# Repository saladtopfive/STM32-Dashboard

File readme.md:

# 🚘 STM32 Go-Kart Dashboard  

> [!IMPORTANT]  
> **Work suspended** — Development suspended as of **07.08.2026**  
> This repository is part of my **Engineering Thesis Project** for the completion of my undergraduate studies.  

## Overview  

This project constitutes the practical component of my **engineering thesis**, focusing on the design and implementation of a **real-time dashboard system** for an electric go-kart.  

The system is developed on the **STM32F746G-DISCO microcontroller** with a touchscreen display using **TouchGFX**, and is intended to collect, process, and visualize telemetry data from multiple hardware sensors.  

The dashboard serves as a **human–machine interface (HMI)**, enabling the driver to monitor essential parameters of the vehicle in real time. These include, but are not limited to:  

## Preview

| Main Screen | Error Table |
|------------|-------------|
|  |  |

| Temperature Table | Battery Table |
|-----------------|----------------|
|  |  |

## Monitored Metrics  

| ***Metric***                | ***Description***                                |
|------------------------|--------------------------------------------|
| **Vehicle Speed**          | Real-time speed display.                   |
| **Throttle / Brake**       | Input level visualization.                  |
| **Battery**                | Voltage and temperature monitoring.         |
| **Motor Temperature**      | Prevents overheating and ensures reliability. |
| **G-Forces**               | Lateral and vertical forces in real time.   |
| **BMS Data (External)**    | Additional telemetry provided by an external Battery Management System (BMS), developed as a separate thesis project. This work only focuses on visualization of the received data. |
| **HOTLAP Button**           | Initiates a lap timer (stopwatch) in the dashboard, showing minutes, seconds, and centiseconds. Useful for tracking lap times during testing or racing sessions. |
| **Future Extensions**      | Additional sensor integrations planned.     |

The objective of this work is to provide a **robust, responsive, and intuitive interface** that supports safe and efficient operation of the electric go-kart.  

## Hardware

As part of the project, a custom **Arduino Shield** is being developed to handle all sensor inputs, signal routing, and electrical interfacing between the go-kart hardware and the STM32 dashboard.  

### KiCad Schematic Preview

### KiCad 3D Model Preview

### IRL pictures

| STM32 - dashboard | Shield |
|------------|-------------|
|  |  |

## Development Notes  

The project was initially developed without version control, with the focus placed on prototyping and interface design. 

As the implementation approaches the stage of **hardware integration**, this repository has been introduced to serve as a platform for:  

- Source code management and tracking.  
- Documentation of development progress. 
- Collaboration and versioning.  

## Roadmap  

| ***Status***    | ***Task*** |
|-----------|------|
|  **Done**   | Acquisition of the go-kart frame. |
|  **Done**   | Development of the UI prototype. |
|  **Ongoing** | Live sensor data implementation. |
|  **Ongoing** | Development of an export data feature. |
|  **Ongoing** | Implementation of battery management visualization. |
|  **Planned** | Integration of BLDC motor control. |

## License
This project is licensed under the MIT permissive license.

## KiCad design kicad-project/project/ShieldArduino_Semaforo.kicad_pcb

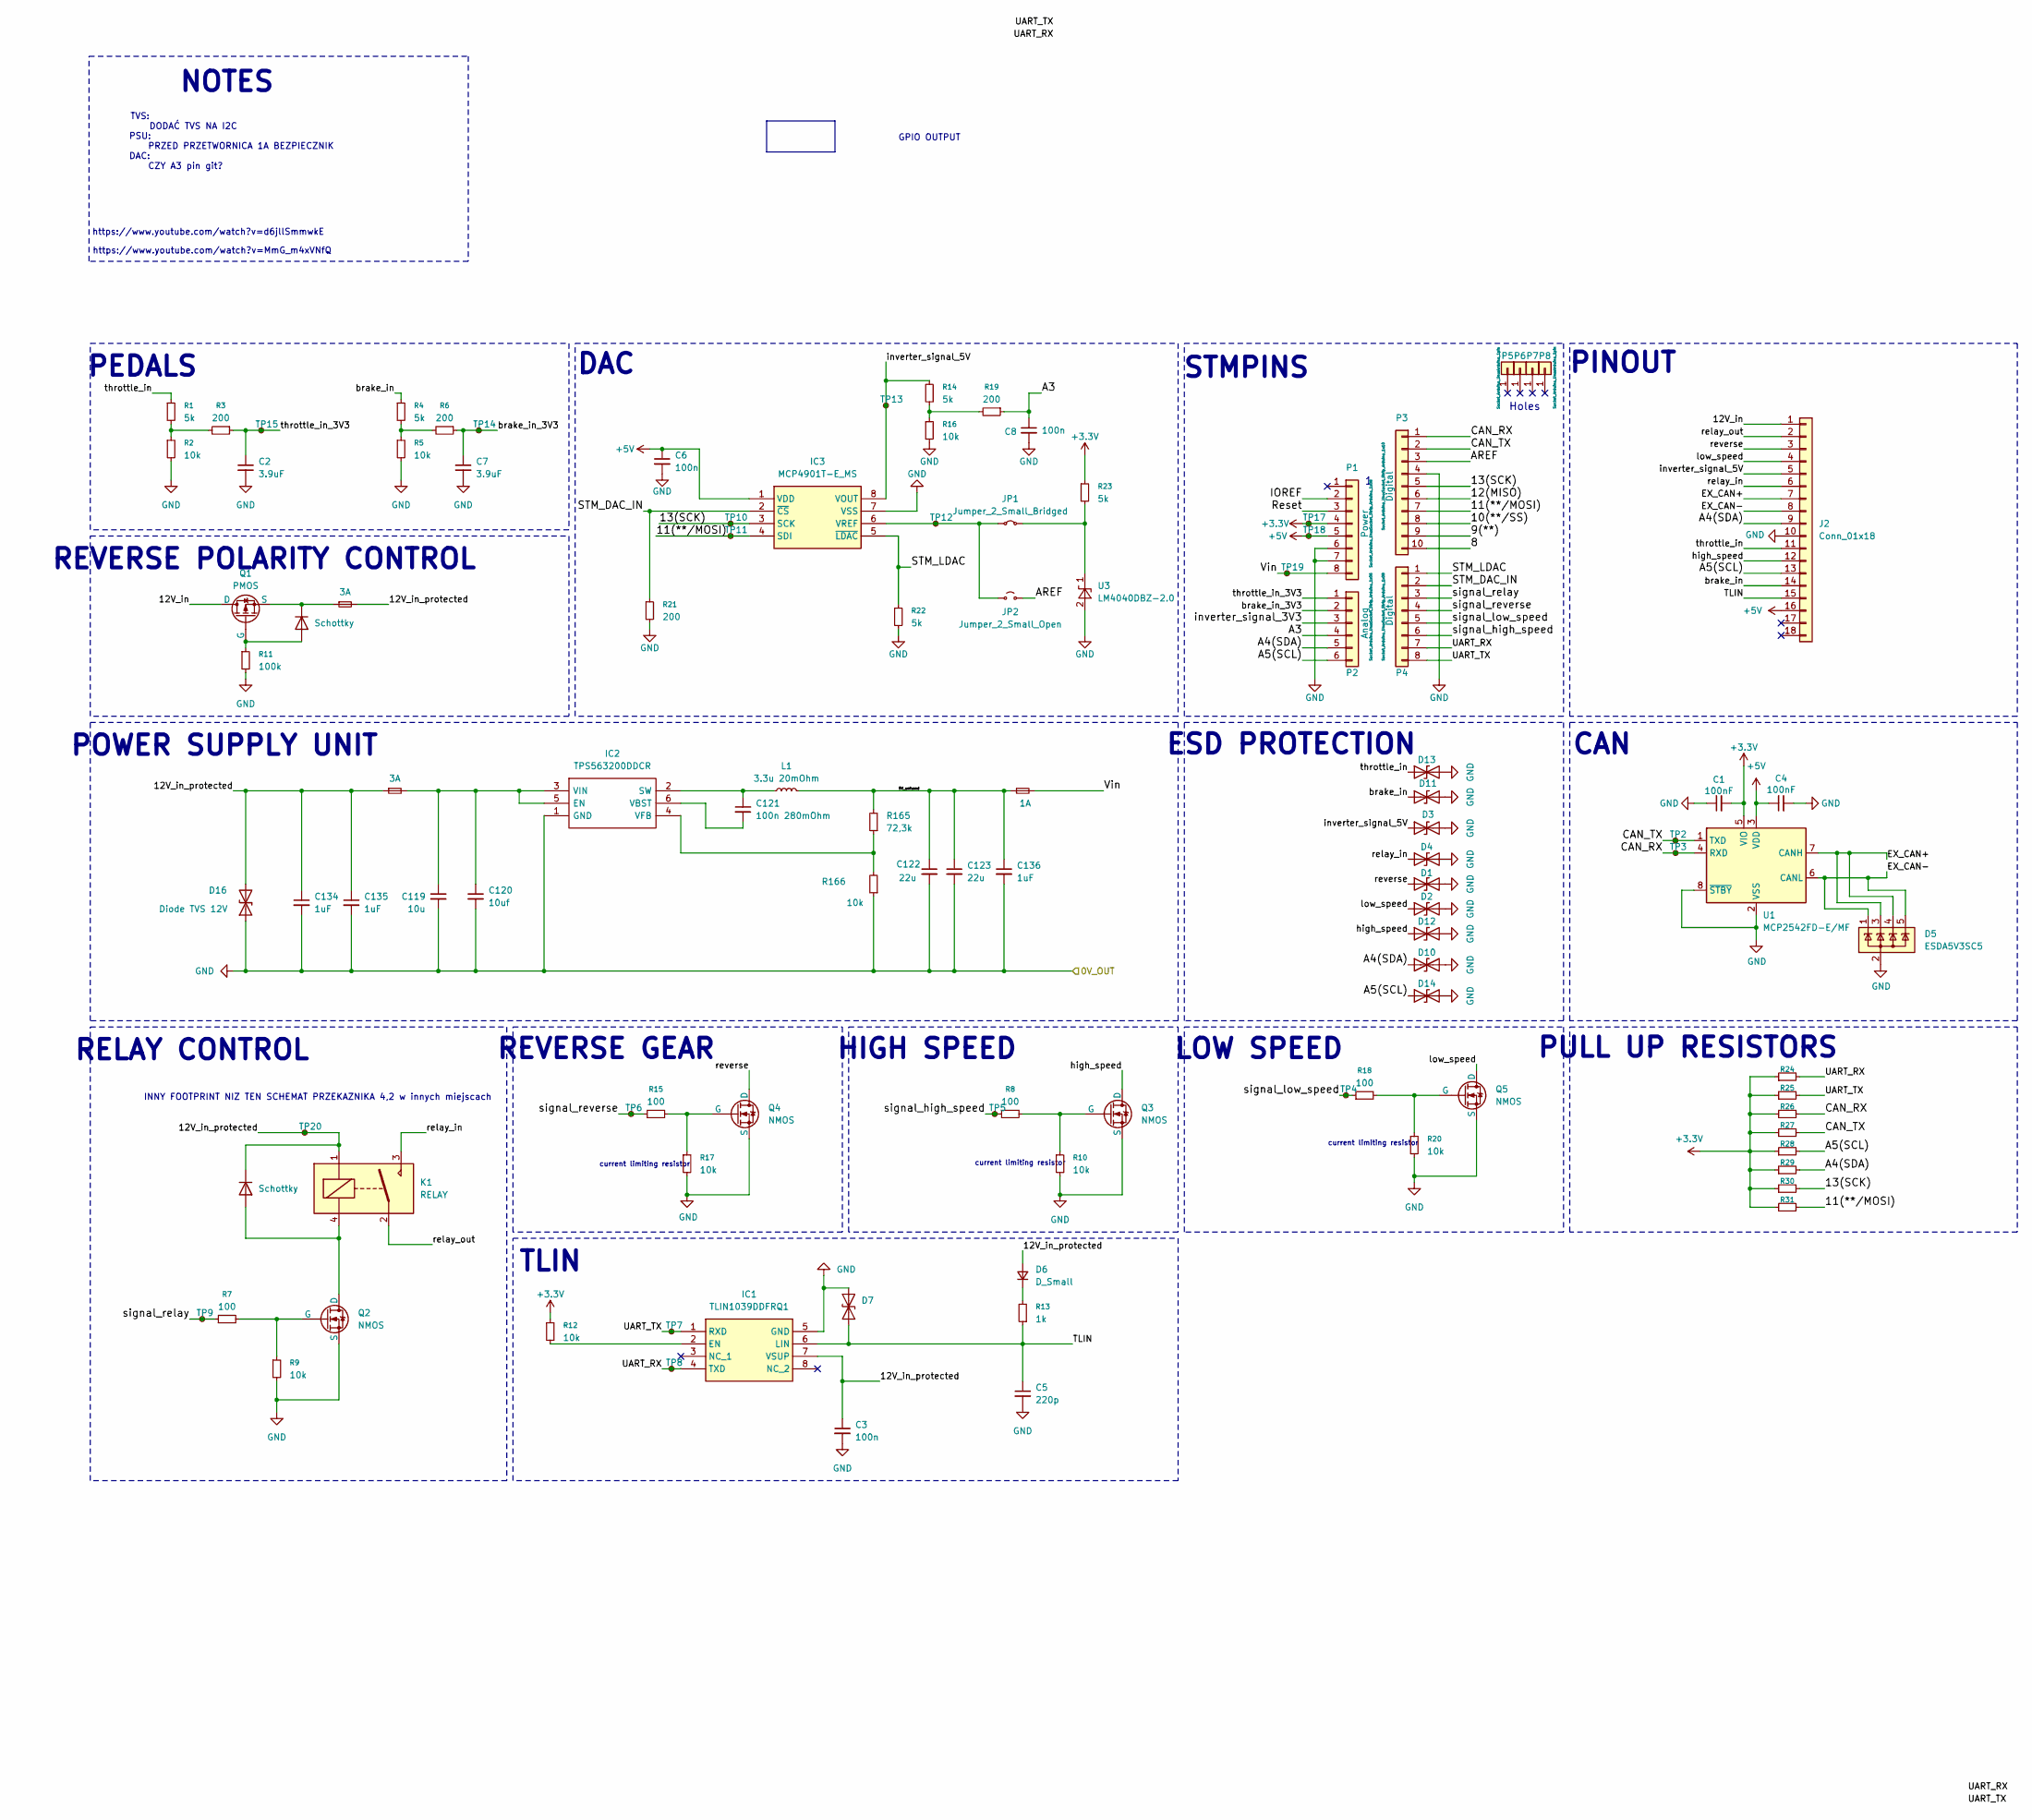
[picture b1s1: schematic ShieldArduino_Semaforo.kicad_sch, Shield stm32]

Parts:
C1, C4: 100nF; C_0603_1608Metric_Pad1.08x0.95mm_HandSolder; Manufacturer_Part_Number --; Mouser Part Number --
C2, C7: 3.9uF; C_1206_3216Metric_Pad1.33x1.80mm_HandSolder
C3, C6, C8: 100n; C_0805_2012Metric_Pad1.18x1.45mm_HandSolder
C5: 220p; C_0805_2012Metric_Pad1.18x1.45mm_HandSolder
C119: 10u; C_0805_2012Metric_Pad1.18x1.45mm_HandSolder
C120: 10uf; C_0805_2012Metric_Pad1.18x1.45mm_HandSolder
C121: 100n 280mOhm; C_0805_2012Metric_Pad1.18x1.45mm_HandSolder
C122, C123: 22u; C_0603_1608Metric_Pad1.08x0.95mm_HandSolder
C134, C135, C136: 1uF; C_0603_1608Metric_Pad1.08x0.95mm_HandSolder
D1, D2, D3, D4, D10, D11, D12, D13, D14: 6V; D_SOD-123F
D5: ESDA5V3SC5; SOT-23-5
D6: D_Small; SODFL3618X100N
D7: ESD131-B1-W0201; SOD2613X100N
D8, D9: Schottky; D_SOD-123
D16: Diode TVS 12V; D_SOD-323_HandSoldering
F1, F3: 3A; Fuse_0603_1608Metric_Pad1.05x0.95mm_HandSolder
F4: 1A; Fuse_0603_1608Metric_Pad1.05x0.95mm_HandSolder
IC1: TLIN1039DDFRQ1; SOT65P280X110-8N; Mouser Part Number 595-TLIN1039DDFRQ1
IC2: TPS563200DDCR; Mouser Part Number 595-TPS563200DDCR
IC3: MCP4901T-E_MS; SOP65P490X110-8N; Mouser Part Number 579-MCP4901T-E/MS
J2: Conn_01x18; M80-54016YY
JP1: Jumper_2_Small_Bridged; SolderJumper-2_P1.3mm_Bridged_RoundedPad1.0x1.5mm
JP2: Jumper_2_Small_Open; SolderJumper-2_P1.3mm_Open_RoundedPad1.0x1.5mm
K1: RELAY; RE034012
L1: 3.3u 20mOhm; CLF7045__
P1: Power; Socket_Strip_Arduino_1x08
P2: Analog; Socket_Strip_Arduino_1x06
P3: Digital; Socket_Strip_Arduino_1x10
P4: Digital; Socket_Strip_Arduino_1x08
P5, P6, P7, P8: CONN_01X01; Arduino_1pin
Q1: PMOS; SOT-23-3
Q2, Q3, Q4, Q5: NMOS; SOT-23-3
R1, R4, R14, R22, R23: 5k; R_0603_1608Metric_Pad0.98x0.95mm_HandSolder
R2, R5, R16, R166: 10k; R_0603_1608Metric_Pad0.98x0.95mm_HandSolder
R3, R6, R19, R21: 200; R_0603_1608Metric_Pad0.98x0.95mm_HandSolder
R7, R8, R15, R18: 100; R_0805_2012Metric_Pad1.20x1.40mm_HandSolder
R9, R10, R12, R17, R20, R24, R25, R26, R27, R28, R29, R30, R31: 10k; R_0805_2012Metric_Pad1.20x1.40mm_HandSolder
R11: 100k; R_0805_2012Metric_Pad1.20x1.40mm_HandSolder
R13: 1k; R_0805_2012Metric_Pad1.20x1.40mm_HandSolder
R165: 72,3k; R_0603_1608Metric_Pad0.98x0.95mm_HandSolder
TP2, TP3, TP4, TP5, TP6, TP7, TP8, TP9, TP10, TP11, TP12, TP13, TP14, TP15, TP17, TP18, TP19, TP20: TestPoint_Small; TestPoint_Pad_D1.5mm
U1: MCP2542FD-E/MF; SOIC127P600X175-8N; Manufacturer_Part_Number MCP2542FD-E/MF; Mouser Part Number 579-MCP2542FD-E/MF
U3: LM4040DBZ-2.0; SOT-23

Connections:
+3.3V: C1.2, P1.4, R12.1, R23.1, R24.1, R25.1, R26.1, R27.1, R28.1, R29.1, R30.1, R31.1, TP17.1, U1.5 (VIO)
+5V: C4.1, C6.1, IC3.1 (VDD), J2.16, P1.5, TP18.1, U1.3 (VDD)
/5V_unfused: C122.1, C123.1, C136.1, F4.1, L1.2, R165.2
/8: P3.10
/9(**): P3.9
/10(**/SS): P3.8
/11(**/MOSI): IC3.4 (SDI), P3.7, R31.2, TP11.1
/12(MISO): P3.6
/12V_in: J2.1, Q1.1 (D)
/12V_in_protected: C3.1, C134.1, C135.1, D6.2 (A), D8.1 (K), D16.2 (A2), F1.2, F3.1, IC1.7 (VSUP), K1.1, TP20.1
/13(SCK): IC3.3 (SCK), P3.5, R30.2, TP10.1
/ relay_in: D4.1 (A1), J2.6, K1.3
/A3: C8.1, P2.4, R19.1
/A4(SDA): D10.1 (A1), J2.9, P2.5, R29.2
/A5(SCL): D14.1 (A1), J2.13, P2.6, R28.2
/AREF: JP2.2 (B), P3.3
/CAN_RX: P3.1, R26.2, TP3.1, U1.4 (RXD)
/CAN_TX: P3.2, R27.2, TP2.1, U1.1 (TXD)
/EX_CAN+: D5.3 (K), D5.4 (K), J2.7, U1.7 (CANH)
/EX_CAN-: D5.1 (K), D5.5 (K), J2.8, U1.6 (CANL)
/IOREF: P1.2
/Reset: P1.3
/STM_DAC_IN: IC3.2 (~CS), P4.2, R21.1
/STM_LDAC: IC3.5 (~LDAC), P4.1, R22.1
/TLIN: C5.1, D7.1 (A1), IC1.6 (LIN), J2.15, R13.1
/UART_RX: IC1.4 (TXD), P4.7, R24.2, TP8.1
/UART_TX: IC1.1 (RXD), P4.8, R25.2, TP7.1
/Vin: F4.2, P1.8, TP19.1
/brake_in: D11.1 (A1), J2.14, R4.1
/brake_in_3V3: C7.1, P2.2, R6.1, TP14.1
/high_speed: D12.1 (A1), J2.12, Q3.1 (D)
/inverter_signal_3V3: P2.3
/inverter_signal_5V: D3.1 (A1), IC3.8 (VOUT), J2.5, R14.1, TP13.1
/low_speed: D2.1 (A1), J2.4, Q5.1 (D)
/relay_out: J2.2, K1.2
/reverse: D1.1 (A1), J2.3, Q4.1 (D)
/signal_high_speed: P4.6, R8.1, TP5.1
/signal_low_speed: P4.5, R18.1, TP4.1
/signal_relay: P4.3, R7.1, TP9.1
/signal_reverse: P4.4, R15.1, TP6.1
/throttle_in: D13.1 (A1), J2.11, R1.1
/throttle_in_3V3: C2.1, P2.1, R3.1, TP15.1
GND: C1.1, C2.2, C3.2, C4.2, C5.2, C6.2, C7.2, C8.2, C119.2, C120.2, C122.2, C123.2, C134.2, C135.2, C136.2, D1.2 (A2), D2.2 (A2), D3.2 (A2), D4.2 (A2), D5.2 (A), D7.2 (A2), D10.2 (A2), D11.2 (A2), D12.2 (A2), D13.2 (A2), D14.2 (A2), D16.1 (A1), IC1.5 (GND), IC2.1 (GND), IC3.7 (VSS), J2.10, P1.6, P1.7, P3.4, Q2.3 (S), Q3.3 (S), Q4.3 (S), Q5.3 (S), R2.2, R5.2, R9.2, R10.2, R11.2, R16.2, R17.2, R20.2, R21.2, R22.2, R166.1, U1.2 (VSS), U1.8 (~STBY), U1.9 (VSS), U3.2 (A)
unnamed: D6.1 (K), R13.2
unnamed: D8.2 (A), K1.4, Q2.1 (D)
unnamed: D9.2 (A), Q1.2 (G), R11.1
unnamed: D9.1 (K), F1.1, Q1.3 (S)
unnamed: IC1.2 (EN), R12.2
unnamed: C119.1, C120.1, F3.2, IC2.3 (VIN), IC2.5 (EN)
unnamed: C121.1, IC2.2 (SW), L1.1
unnamed: C121.2, IC2.6 (VBST)
unnamed: IC2.4 (VFB), R165.1, R166.2
unnamed: IC3.6 (VREF), JP1.1 (A), JP2.1 (A), TP12.1
unnamed: JP1.2 (B), R23.2, U3.1 (K)
unnamed: Q2.2 (G), R7.2, R9.1
unnamed: Q3.2 (G), R8.2, R10.1
unnamed: Q4.2 (G), R15.2, R17.1
unnamed: Q5.2 (G), R18.2, R20.1
unnamed: R1.2, R2.1, R3.2
unnamed: R4.2, R5.1, R6.2
unnamed: R14.2, R16.1, R19.2

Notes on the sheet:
PSU: PRZED PRZETWORNICA 1A BEZPIECZNIK DAC: CZY A3 pin git?
DAC
current limiting resistor
ESD PROTECTION
TLIN
POWER SUPPLY UNIT
Holes
LOW SPEED
REVERSE POLARITY CONTROL
https://www.youtube.com/watch?v=d6jllSmmwkE
TVS: DODAĆ TVS NA I2C
REVERSE GEAR
NOTES
GPIO OUTPUT
CAN
PEDALS
PULL UP RESISTORS
HIGH SPEED
PINOUT
RELAY CONTROL
https://www.youtube.com/watch?v=MmG_m4xVNfQ
INNY FOOTPRINT NIZ TEN SCHEMAT PRZEKAZNIKA 4,2 w innych miejscach
STMPINS

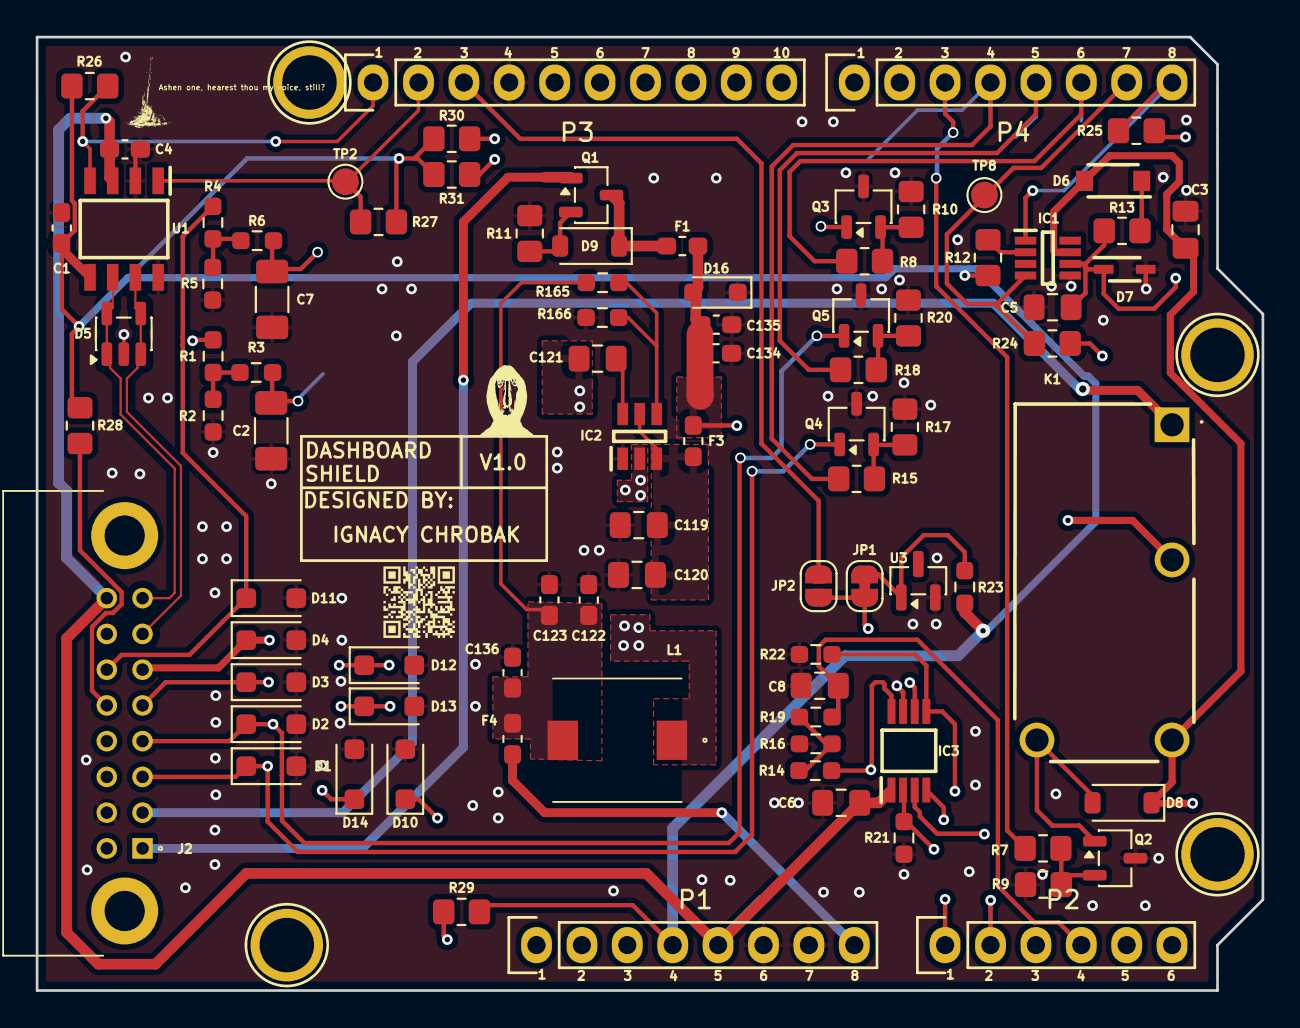
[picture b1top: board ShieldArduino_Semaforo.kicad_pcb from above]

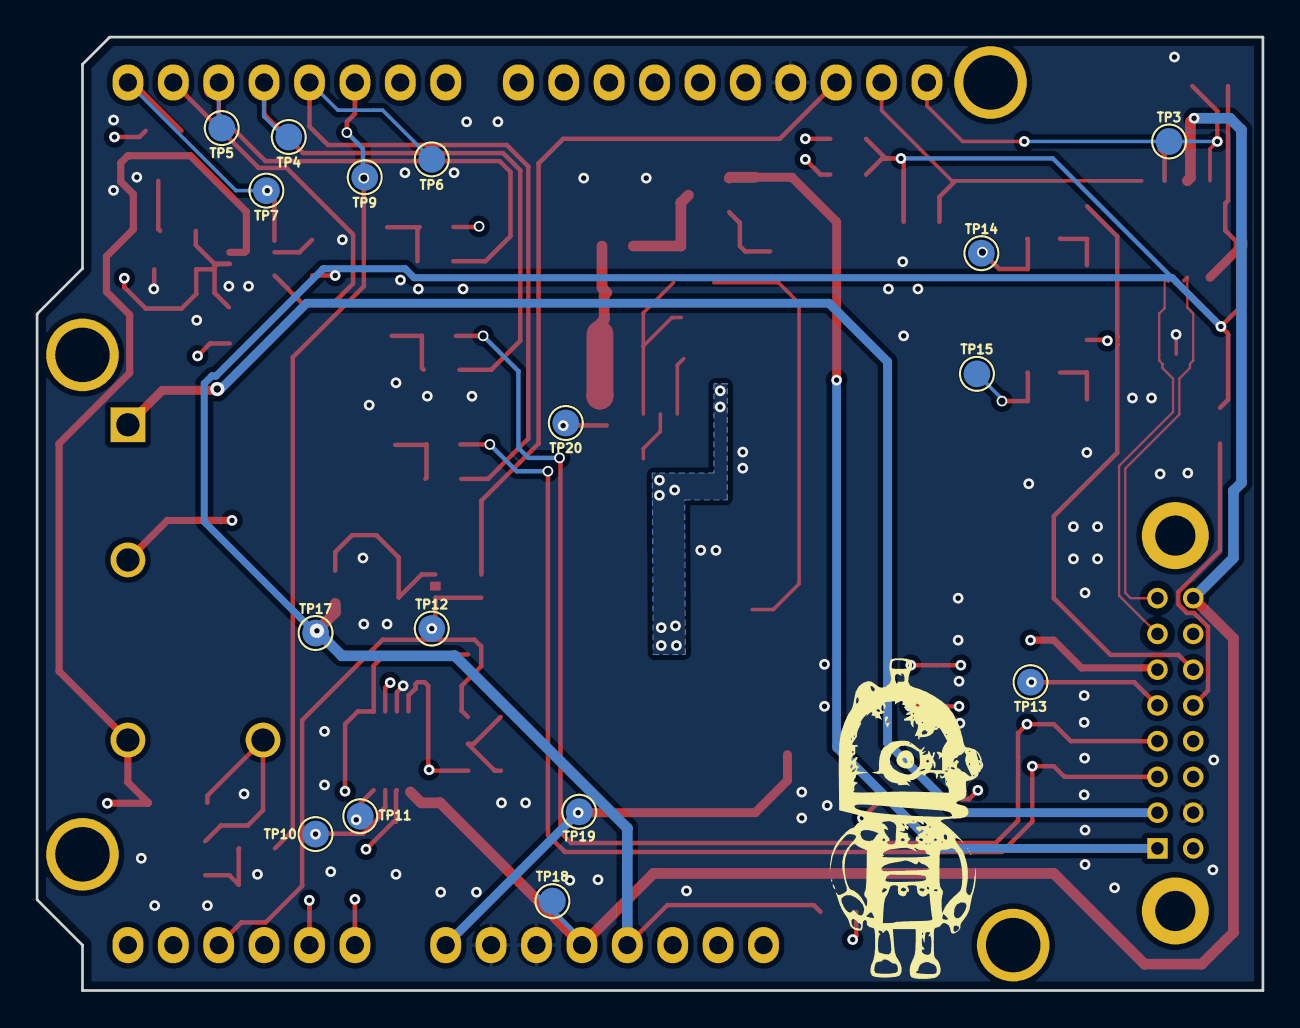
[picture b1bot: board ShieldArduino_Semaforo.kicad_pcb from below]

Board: 4 copper layers, 68.6 x 53.3 mm, 108 parts (16 on the bottom side), 54 nets.

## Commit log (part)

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2025-05-06 added necesarry files + gitignore
2025-05-06 updated some comments
2025-05-06 test file name change v1
2025-05-06 changed it back
2025-05-06 testing
2025-05-06 readme updated
2025-05-06 added missing readme
2025-05-06 readme fuckups
2025-06-15 changed the layout of the base screens
2025-08-21 GFX-dashboard-v0.1
2025-08-21 readme-overhaul
2025-08-21 readme.md-overhaul-v2
2025-09-17 gitignore-update
2025-09-17 readme-update
2025-09-17 gitignore-removal
2025-09-17 gitignore-added
2025-09-29 total-overhaul
2025-09-29 test
2025-09-29 overhaulv0.1
2025-09-29 overhaulv0.2
2025-09-29 dashboard-layout-v1.0
2025-10-11 dashboard-overhaul-v0.2
2025-10-11 dashboard-clockwork
2025-10-11 dasboard-hotlap-v1.0
2025-10-11 dashboard-batterypanel
2025-10-11 readme-dashboard-preview
2025-10-11 readme-date-update
2025-10-11 readme-youtube
2025-10-11 readme-youtube-fix
2025-10-11 dashboard-minorfixes
2025-10-14 dashboard-change_screen_btn
2025-10-19 dashboard-shield-v0.1
2025-10-22 dashboard-temp_table-v1.0
2025-10-22 dashboard-battery_table-v1.0
2025-10-22 dashboard-battery_table-v1.1
2025-10-22 dashboard-temperature_table-v1.1
2025-10-22 dashboard-battery_table-v1.2
2025-10-22 dashboard-error_table-v1.0
2025-10-22 dashboard-error_table-relay_button
2025-10-22 readme-preview_pngs
2025-10-22 readme-screen_preview
2025-10-22 readme-screen_preview_update
2025-10-22 readme-screen_preview-fix
2025-10-22 readme-screen_preview-fixv2
2025-10-23 reamde-fix
    Removed Motor Driver Status from the feature list.
2025-10-23 readme-dir
2025-10-23 readme-img-fix
2025-10-23 tetst
2025-10-23 test3
2025-10-23 readme-fix??
2025-10-23 Fix image dimensions in preview section
2025-10-23 Fix image dimensions in readme.md tables
2025-10-27 shield-prototype-v1.2
2025-10-27 kicad-schematics-v1.2
2025-10-28 kicad_schematic-cleanup
2025-11-12 screen3,4-update
2025-11-12 tvs_fuse-kicad
2025-11-12 pcb-tweaks
2025-11-12 kicad-reverse_polarity_pinout_tvs-update
2025-11-13 kicad-tvs_psu_pinout-update
2025-11-13 pcb-tests
2025-11-14 kicad-schematic_cleanup
2025-11-14 kicad-relay_transistor_pcb-layout
2025-11-14 kicad-pcb_work
2025-11-14 kicad-work
2025-11-16 kicad-pcb
2025-11-16 kicad-project-layout-v0.5
2025-11-16 merge-conflict-fix
2025-11-16 kicad-pcb-layout-v0.6
2025-11-16 kicad-project-layout-v0.7
2025-11-16 kicad-pcb-layout-v0.8
2025-11-16 kicad-pcb-layout-v0.8.1
2025-11-17 kicad-pcb-layout-v0.9
2025-11-17 kicad-pcb-layout-v0.9.1
2025-11-17 kicad-pcb-layout-v1.0
2025-11-17 kicad-pcb-layout-v1.0.1
2025-11-17 merge
2025-11-17 merge2
2025-11-17 gitignore
2025-11-18 readme-pcb-update
2025-11-18 readme-license
2025-11-18 license
2025-11-18 kicad-pcb-layout-v1.0.2
2025-11-18 kicad-pcb-layout-v1.0.3
2025-11-18 kicad-pcb-layout-v1.0.4
2025-11-18 kicad-pcb-layout-v1.0.5
2025-11-18 kicad-pcb-layout-v1.0.7
2025-11-18 kicad-pcb-layout-v1.0.8
2025-11-19 _prl
2025-11-19 kicad-pcb-layout-v1.0.9
2025-11-19 Dodano test pointy na kazdym sensownym do pomiaru miejscu, dodano przelotki do masy - ground stitching
2025-11-20 kciad-schematic-tlin
2025-11-20 kicad-schematic-tlin2
2025-11-20 kicad-schemat-work
2025-11-20 kicad-pcb-layout-v1.1.0
2025-11-20 kicad-pcb-layout-v1.1.1
2025-11-20 kicad-pcb-layout-v1.1.2
2025-11-20 kicad-pcb-silk_layer_cleanup
2025-11-21 kicad-pcb-images
2025-11-21 kicad-images
2025-11-21 kicad-pcb-relay_change
2025-11-21 pcb-gerber-v1.0.0
2025-11-21 footprint-fixes
2025-11-25 dashboard-mounting_plate-model-v0.1
2025-11-25 dashboard-mounting_plate-model-v0.2
2025-12-01 added peripheral files
2025-12-01 freecad-mountingplate_work
2025-12-01 readme-3d/schematic addition
2025-12-01 Include KiCad schematic and 3D model previews in README
    Added previews for KiCad schematic and 3D model.
2025-12-15 .prl
2025-12-15 freecad-added measurement stls and mounting plate work
2026-01-01 freecad-work
2026-01-06 schematic-cleanup
2026-01-06 Replace KiCad schematic and 3D model images
    Updated images for KiCad schematic and 3D model previews in the README.
2026-01-13 added gear selector
2026-01-13 error screen update
2026-01-13 more error screen updates
2026-01-13 updating the temperature table screen
2026-01-13 temperature table screen updated
2026-01-13 irl pics included
2026-01-17 Shield by Tadeusz Zakola
2026-01-18 Add IRL pictures section to README
    Added a section for IRL pictures of the STM32 dashboard and shield.
2026-01-18 Update work in progress date in README
2026-01-18 .zip error fix
